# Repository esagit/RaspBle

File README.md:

# RaspBle
RN4020 BLE Module Breakout Board for Raspberry Pi 2 model B
* [Microchip RN4020 BLE Module](http://www.microchip.com/wwwproducts/en/RN4020)

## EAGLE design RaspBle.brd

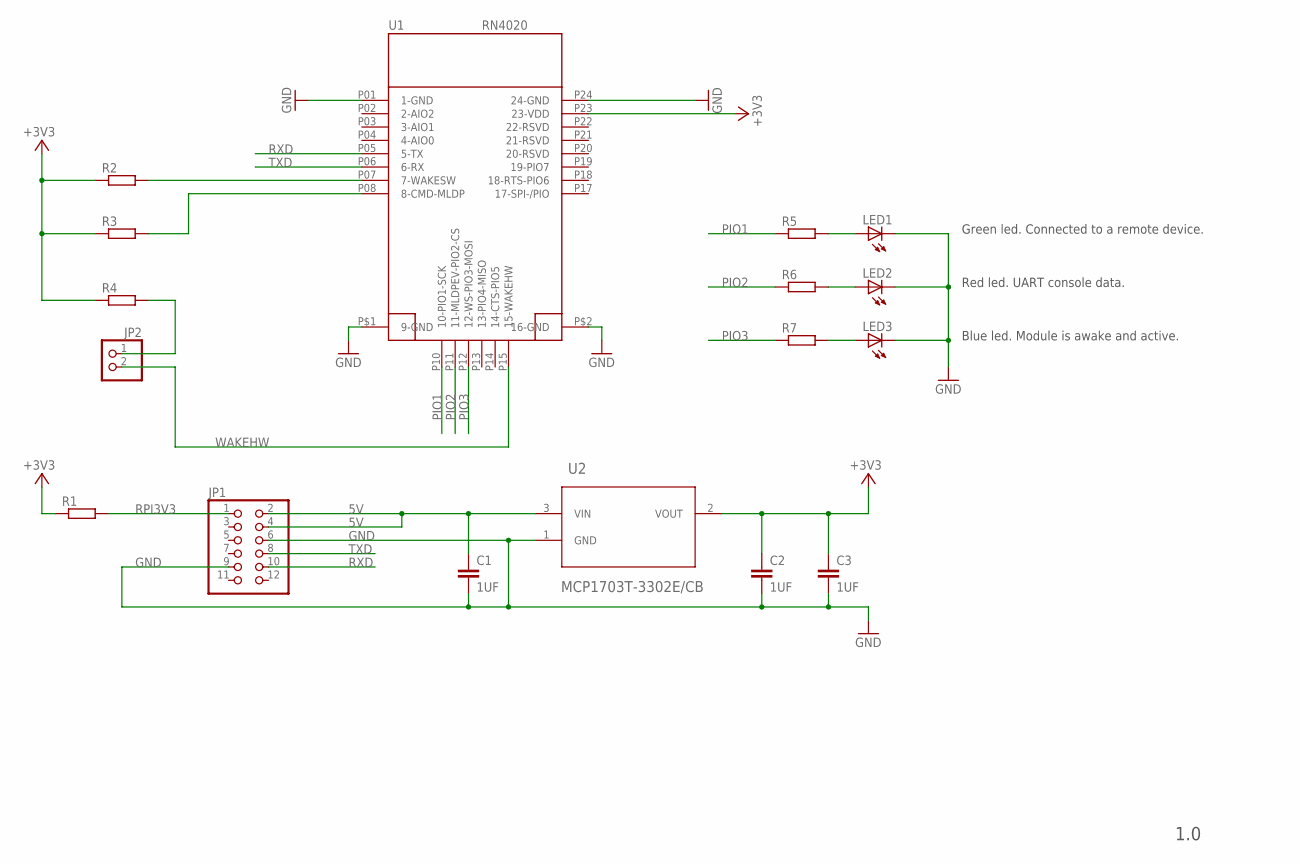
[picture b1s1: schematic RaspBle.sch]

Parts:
C1, C2, C3: 1UF; C1206
JP1: PINHD-2X6; 2X06
JP2: PINHD-1X2; 1X02
LED1, LED2, LED3: LEDSML1206; SML1206
R1, R2, R3, R4, R5, R6, R7: R-EU_R1206; R1206
U1: RN4020; RN4020SMD
U2: MCP1703T-3302E/CB; SOT95P300X145-3N

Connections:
5V: C1.1, JP1.2, JP1.4, U2.3 (VIN)
+3V3: C2.1, C3.1, R1.1, R2.1, R3.1, R4.1, U1.P23 (23-VDD), U2.2 (VOUT)
GND: C1.2, C2.2, C3.2, JP1.6, JP1.9, LED1.C, LED2.C, LED3.C, U1.P01 (1-GND), U1.P24 (24-GND), U1.P$1 (9-GND), U1.P$2 (16-GND), U2.1 (GND)
unnamed: R2.2, U1.P07 (7-WAKESW)
unnamed: R3.2, U1.P08 (8-CMD-MLDP)
unnamed: JP2.1, R4.2
unnamed: LED3.A, R7.2
unnamed: LED2.A, R6.2
unnamed: LED1.A, R5.2
PIO1: R5.1, U1.P10 (10-PIO1-SCK)
PIO2: R6.1, U1.P11 (11-MLDPEV-PIO2-CS)
PIO3: R7.1, U1.P12 (12-WS-PIO3-MOSI)
RPI3V3: JP1.1, R1.2
RXD: JP1.10, U1.P05 (5-TX)
TXD: JP1.8, U1.P06 (6-RX)
WAKEHW: JP2.2, U1.P15 (15-WAKEHW)

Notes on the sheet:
Green led. Connected to a remote device.
Red led. UART console data.
Blue led. Module is awake and active.
1.0

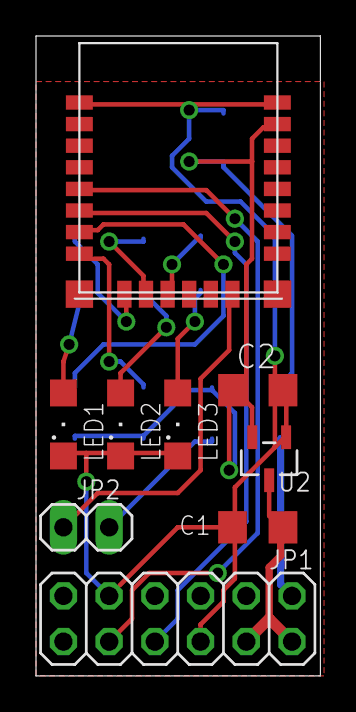
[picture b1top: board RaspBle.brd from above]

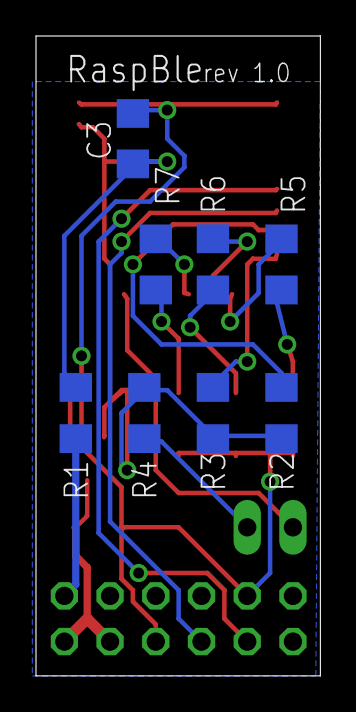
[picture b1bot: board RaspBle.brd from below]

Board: 2 copper layers, 15.8 x 35.5 mm, 17 parts (8 on the bottom side), 16 nets.

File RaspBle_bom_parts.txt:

Partlist exported from C:/Users/Esa/Documents/eagle/RaspBle/RaspBle.sch at 23.8.2017 22.49

Part Value             Device            Package          Description                         MPN               OC_FARNELL OC_NEWARK PACKAGE SUPPLIER 
C1   1UF               C-EUC1206         C1206            CAPACITOR, European symbol                                                                  
C2   1UF               C-EUC1206         C1206            CAPACITOR, European symbol                                                                  
C3   1UF               C-EUC1206         C1206            CAPACITOR, European symbol                                                                  
JP1                    PINHD-2X6         2X06             PIN HEADER                                                                                  
JP2                    PINHD-1X2         1X02             PIN HEADER                                                                                  
LED1                   LEDSML1206        SML1206          LED                                                                                         
LED2                   LEDSML1206        SML1206          LED                                                                                         
LED3                   LEDSML1206        SML1206          LED                                                                                         
R1                     R-EU_R1206        R1206            RESISTOR, European symbol                                                                   
R2                     R-EU_R1206        R1206            RESISTOR, European symbol                                                                   
R3                     R-EU_R1206        R1206            RESISTOR, European symbol                                                                   
R4                     R-EU_R1206        R1206            RESISTOR, European symbol                                                                   
R5                     R-EU_R1206        R1206            RESISTOR, European symbol                                                                   
R6                     R-EU_R1206        R1206            RESISTOR, European symbol                                                                   
R7                     R-EU_R1206        R1206            RESISTOR, European symbol                                                                   
U1   RN4020            RN4020            RN4020SMD                                                                                                    
U2   MCP1703T-3302E/CB MCP1703T-3302E/CB SOT95P300X145-3N Low Quiescent Current LDO Regulator MCP1703T-3302E/CB 1439518    40M0637   SOT-3   Microchip

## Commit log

2017-08-23 :circus_tent: Added .gitattributes & .gitignore files
2017-08-23 Rev A and pdf files added
2017-08-24 Updated .cam files
